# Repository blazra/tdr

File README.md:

# TDR
TDR using Lattice ECP5 High Data Rate Transceiver

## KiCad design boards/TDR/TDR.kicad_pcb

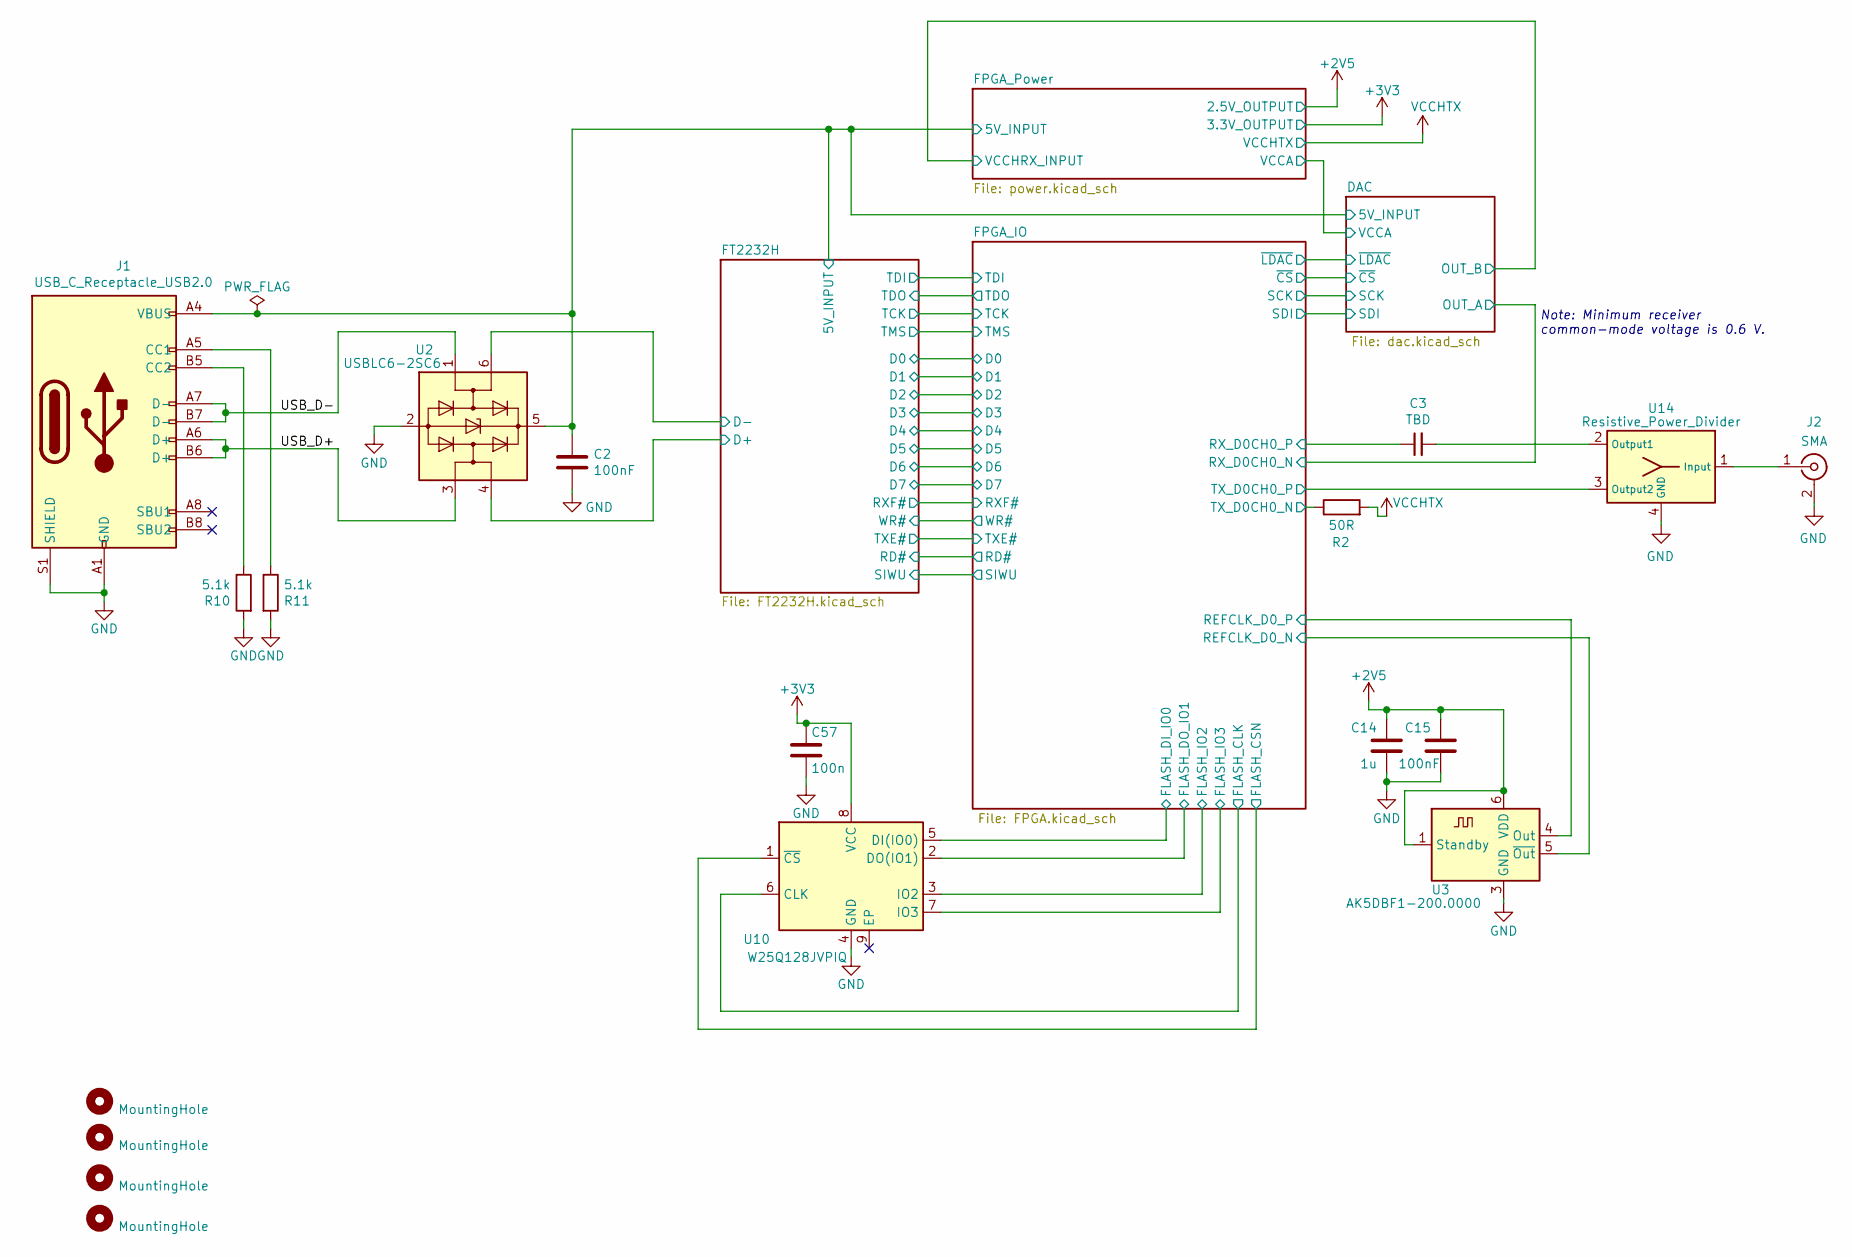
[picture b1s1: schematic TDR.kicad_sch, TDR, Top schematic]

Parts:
C2, C15: 100nF; C_0402_1005Metric
C3: TBD; C_0402_1005Metric
C14: 1u; C_0805_2012Metric
C57: 100n; C_0402_1005Metric
H1, H2, H3, H4: MountingHole; MountingHole_3.2mm_M3
J1: USB_C_Receptacle_USB2.0; USB_C_Receptacle_JAE_DX07S016
J2: SMA; Rosenberger_SMA_32K243-40ML5
R2: 50R; R_0402_1005Metric
R10, R11: 5.1k; R_0805_2012Metric
U2: USBLC6-2SC6; SOT-23-6
U3: AK5DBF1-200.0000; Oscillator_SMD_IDT_JS6-6_5.0x3.2mm_P1.27mm
U10: W25Q128JVPIQ; WSON-8-1EP_6x5mm_P1.27mm_EP3.4x4.3mm
U14: Resistive_Power_Divider; Susumu_PS2012G

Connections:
+2V5: C14.1, C15.1, U3.1 (Standby), U3.6 (VDD); also elsewhere on the board
+3V3: C57.1, U10.8 (VCC); also elsewhere on the board
/5V_INPUT: C2.1, J1.A4 (VBUS), J1.A9 (VBUS), J1.B4 (VBUS), J1.B9 (VBUS), U2.5 (VBUS); also elsewhere on the board
/D+: U2.4 (I/O2); also elsewhere on the board
/D-: U2.6 (I/O1); also elsewhere on the board
/FLASH_CLK: U10.6 (CLK); also elsewhere on the board
/FLASH_CSN: U10.1 (~CS); also elsewhere on the board
/FLASH_DI_IO0: U10.5 (DI(IO0)); also elsewhere on the board
/FLASH_DO_IO1: U10.2 (DO(IO1)); also elsewhere on the board
/FLASH_IO2: U10.3 (IO2); also elsewhere on the board
/FLASH_IO3: U10.7 (IO3); also elsewhere on the board
/REFCLK_D0_N: U3.5 (~Out); also elsewhere on the board
/REFCLK_D0_P: U3.4 (Out); also elsewhere on the board
/RX_D0CH0_P: C3.1; also elsewhere on the board
/TX_D0CH0_N: R2.1; also elsewhere on the board
/TX_D0CH0_P: U14.3 (Output2); also elsewhere on the board
/USB_D+: J1.A6 (D+), J1.B6 (D+), U2.3 (I/O2)
/USB_D-: J1.A7 (D-), J1.B7 (D-), U2.1 (I/O1)
GND: C2.2, C14.2, C15.2, C57.2, J1.A1 (GND), J1.A12 (GND), J1.B1 (GND), J1.B12 (GND), J1.S1 (SHIELD), J2.2 (Ext), R10.2, R11.2, U2.2 (GND), U3.3 (GND), U10.4 (GND), U14.4 (GND); also elsewhere on the board
unnamed: C3.2, U14.2 (Output1)
unnamed: J1.A5 (CC1), R11.1
unnamed: J1.B5 (CC2), R10.1
unnamed: J2.1 (In), U14.1 (Input)
VCCHTX: R2.2; also elsewhere on the board

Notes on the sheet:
Note: Minimum receiver common-mode voltage is 0.6 V.

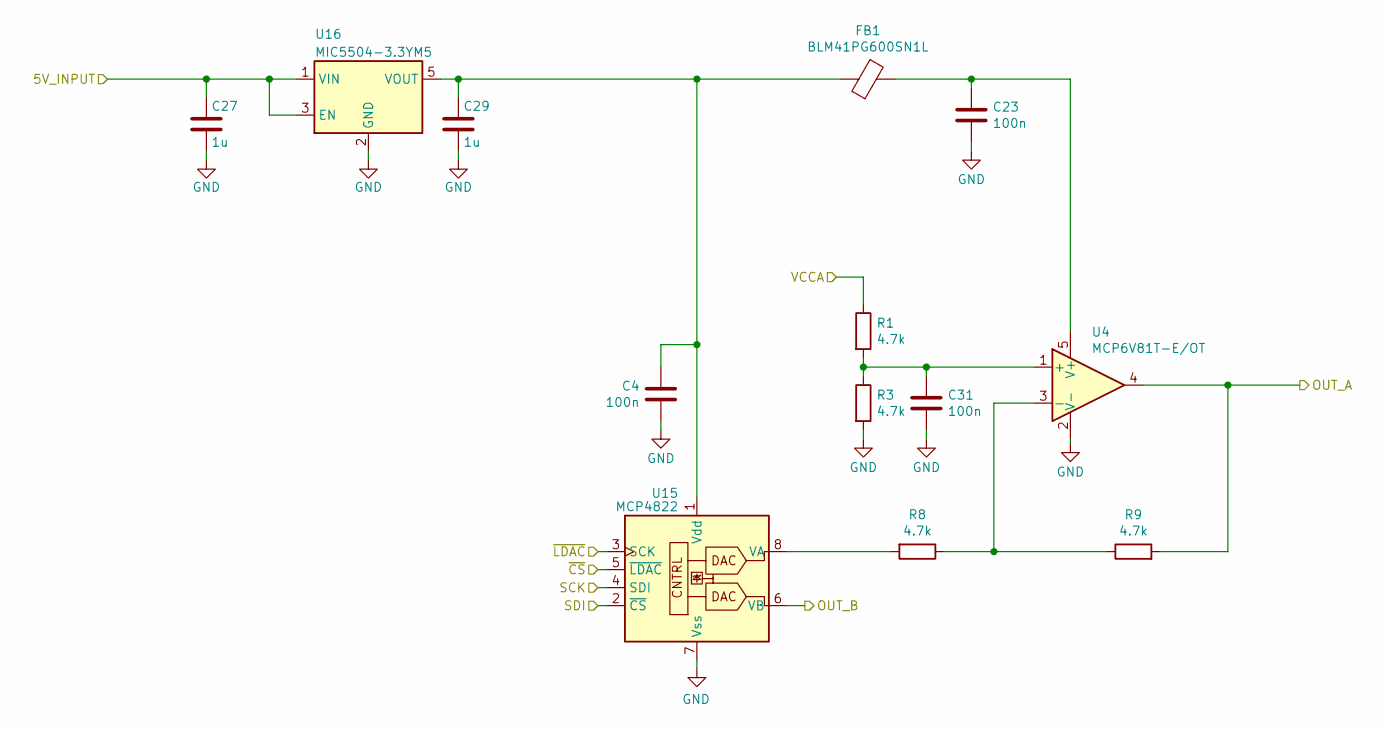
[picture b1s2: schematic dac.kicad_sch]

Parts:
C4, C23, C31: 100n; C_0402_1005Metric
C27, C29: 1u; C_0805_2012Metric
FB1: BLM41PG600SN1L; L_1806_4516Metric
R1, R3, R8, R9: 4.7k; R_0805_2012Metric
U4: MCP6V81T-E/OT; SOT-23-5
U15: MCP4822; MSOP-8_3x3mm_P0.65mm
U16: MIC5504-3.3YM5; SOT-23-5

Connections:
/5V_INPUT: C27.1, U16.1 (VIN), U16.3 (EN); also elsewhere on the board
/OUT_A: R9.2, U4.4; also elsewhere on the board
/OUT_B: U15.6 (VB); also elsewhere on the board
/SCK: U15.4 (SDI); also elsewhere on the board
/SDI: U15.2 (~CS); also elsewhere on the board
/VCCA: R1.1; also elsewhere on the board
/~CS: U15.5 (~LDAC); also elsewhere on the board
/~LDAC: U15.3 (SCK); also elsewhere on the board
GND: C4.2, C23.2, C27.2, C29.2, C31.1, R3.2, U4.2 (V-), U15.7 (Vss), U16.2 (GND); also elsewhere on the board
unnamed: C23.1, FB1.2, U4.5 (V+)
unnamed: C4.1, C29.1, FB1.1, U15.1 (Vdd), U16.5 (VOUT)
unnamed: C31.2, R1.2, R3.1, U4.1 (+)
unnamed: R8.1, R9.1, U4.3 (-)
unnamed: R8.2, U15.8 (VA)

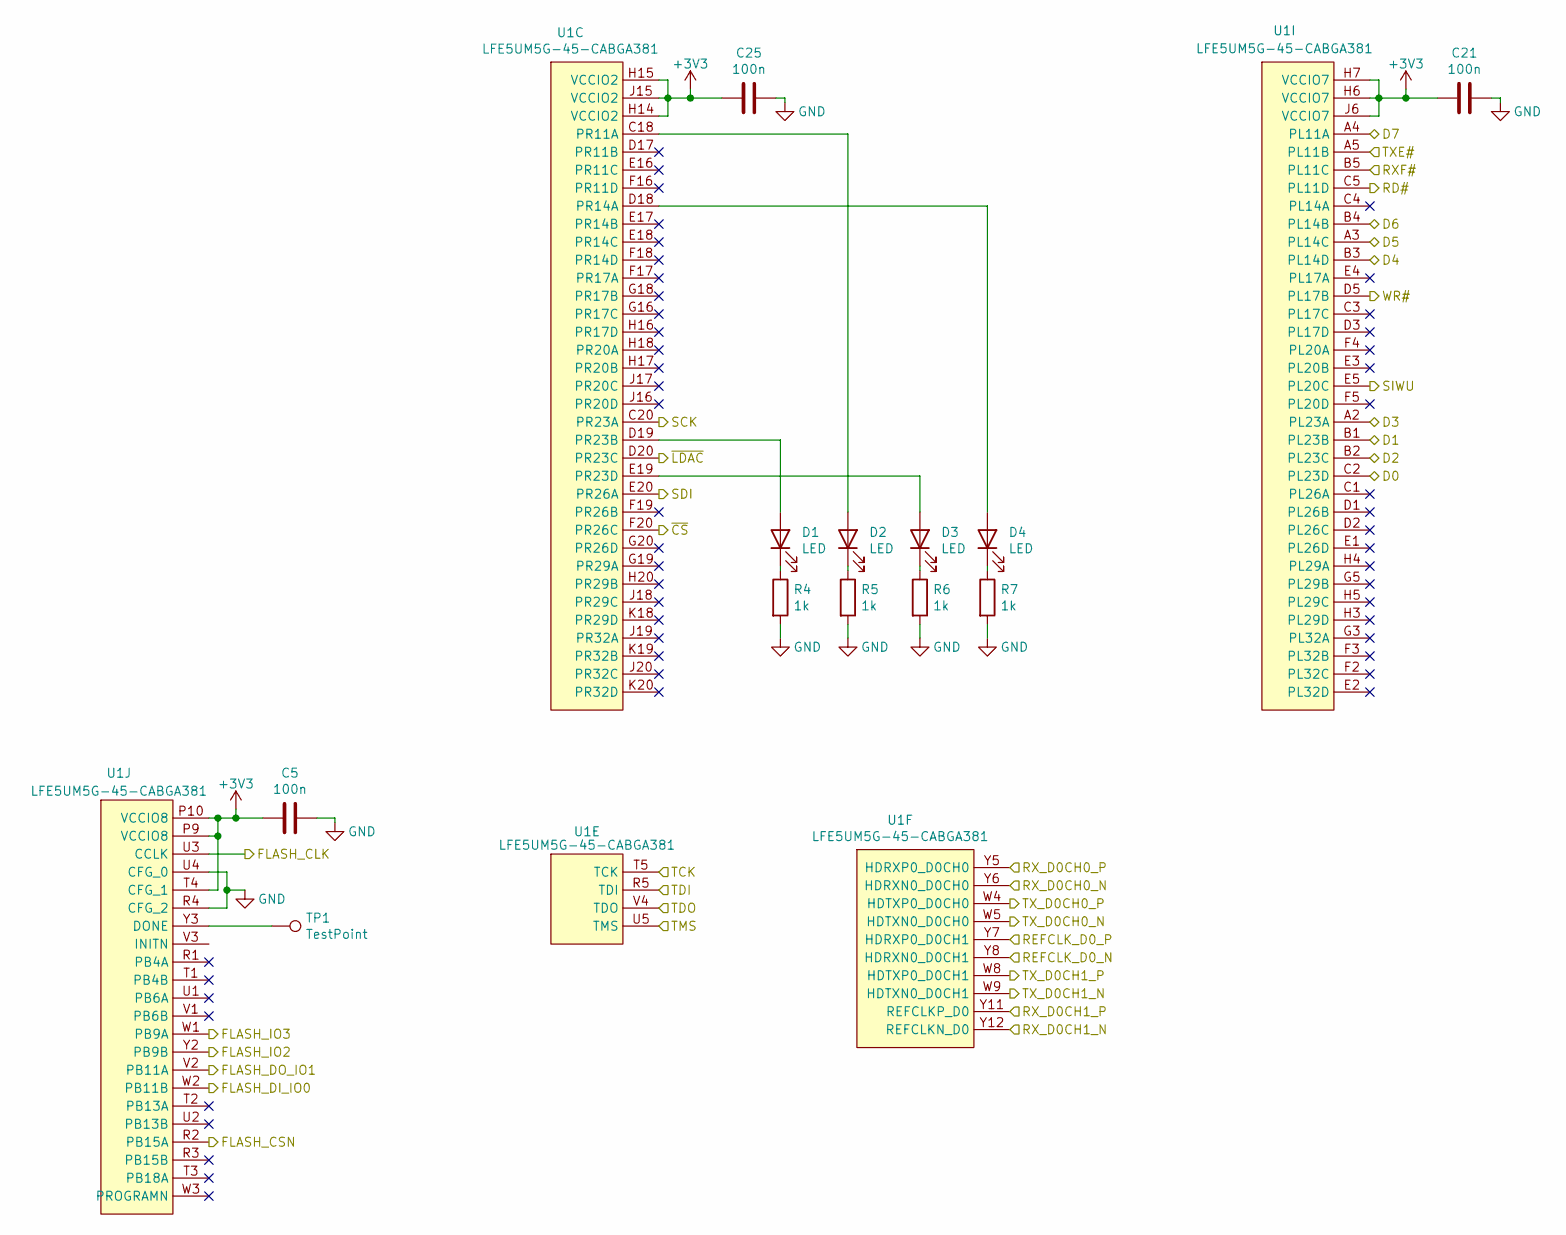
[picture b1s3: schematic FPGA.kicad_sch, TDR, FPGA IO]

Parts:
C5, C21, C25: 100n; C_0402_1005Metric
D1, D2, D3, D4: LED; LED_0805_2012Metric_Castellated
R4, R5, R6, R7: 1k; R_0805_2012Metric
TP1: TestPoint; TestPoint_Pad_D1.0mm
U1: LFE5UM5G-45-CABGA381; Lattice_caBGA-381_17.0x17.0mm_Layout20x20_P0.8mm_Ball0.4mm_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

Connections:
+3V3: C5.1, C21.1, C25.1, U1.H6 (VCCIO7), U1.H7 (VCCIO7), U1.H14 (VCCIO2), U1.H15 (VCCIO2), U1.J6 (VCCIO7), U1.J15 (VCCIO2), U1.P9 (VCCIO8), U1.P10 (VCCIO8), U1.T4 (CFG_1); also elsewhere on the board
/D0: U1.C2 (PL23D); also elsewhere on the board
/D1: U1.B1 (PL23B); also elsewhere on the board
/D2: U1.B2 (PL23C); also elsewhere on the board
/D3: U1.A2 (PL23A); also elsewhere on the board
/D4: U1.B3 (PL14D); also elsewhere on the board
/D5: U1.A3 (PL14C); also elsewhere on the board
/D6: U1.B4 (PL14B); also elsewhere on the board
/D7: U1.A4 (PL11A); also elsewhere on the board
/FLASH_CLK: U1.U3 (CCLK); also elsewhere on the board
/FLASH_CSN: U1.R2 (PB15A); also elsewhere on the board
/FLASH_DI_IO0: U1.W2 (PB11B); also elsewhere on the board
/FLASH_DO_IO1: U1.V2 (PB11A); also elsewhere on the board
/FLASH_IO2: U1.Y2 (PB9B); also elsewhere on the board
/FLASH_IO3: U1.W1 (PB9A); also elsewhere on the board
/FPGA_IO/RX_D0CH1_N: U1.Y12 (REFCLKN_D0)
/FPGA_IO/RX_D0CH1_P: U1.Y11 (REFCLKP_D0)
/FPGA_IO/TX_D0CH1_N: U1.W9 (HDTXN0_D0CH1)
/FPGA_IO/TX_D0CH1_P: U1.W8 (HDTXP0_D0CH1)
/OUT_A: U1.Y6 (HDRXN0_D0CH0); also elsewhere on the board
/RD#: U1.C5 (PL11D); also elsewhere on the board
/REFCLK_D0_N: U1.Y8 (HDRXN0_D0CH1); also elsewhere on the board
/REFCLK_D0_P: U1.Y7 (HDRXP0_D0CH1); also elsewhere on the board
/RXF#: U1.B5 (PL11C); also elsewhere on the board
/RX_D0CH0_P: U1.Y5 (HDRXP0_D0CH0); also elsewhere on the board
/SCK: U1.C20 (PR23A); also elsewhere on the board
/SDI: U1.E20 (PR26A); also elsewhere on the board
/SIWU: U1.E5 (PL20C); also elsewhere on the board
/TCK: U1.T5 (TCK); also elsewhere on the board
/TDI: U1.R5 (TDI); also elsewhere on the board
/TDO: U1.V4 (TDO); also elsewhere on the board
/TMS: U1.U5 (TMS); also elsewhere on the board
/TXE#: U1.A5 (PL11B); also elsewhere on the board
/TX_D0CH0_N: U1.W5 (HDTXN0_D0CH0); also elsewhere on the board
/TX_D0CH0_P: U1.W4 (HDTXP0_D0CH0); also elsewhere on the board
/WR#: U1.D5 (PL17B); also elsewhere on the board
/~CS: U1.F20 (PR26C); also elsewhere on the board
/~LDAC: U1.D20 (PR23C); also elsewhere on the board
GND: C5.2, C21.2, C25.2, R4.2, R5.2, R6.2, R7.2, U1.R4 (CFG_2), U1.U4 (CFG_0); also elsewhere on the board
unnamed: D1.1 (K), R4.1
unnamed: D1.2 (A), U1.D19 (PR23B)
unnamed: D2.1 (K), R5.1
unnamed: D2.2 (A), U1.C18 (PR11A)
unnamed: D3.1 (K), R6.1
unnamed: D3.2 (A), U1.E19 (PR23D)
unnamed: D4.1 (K), R7.1
unnamed: D4.2 (A), U1.D18 (PR14A)
unnamed: TP1.1, U1.Y3 (DONE)

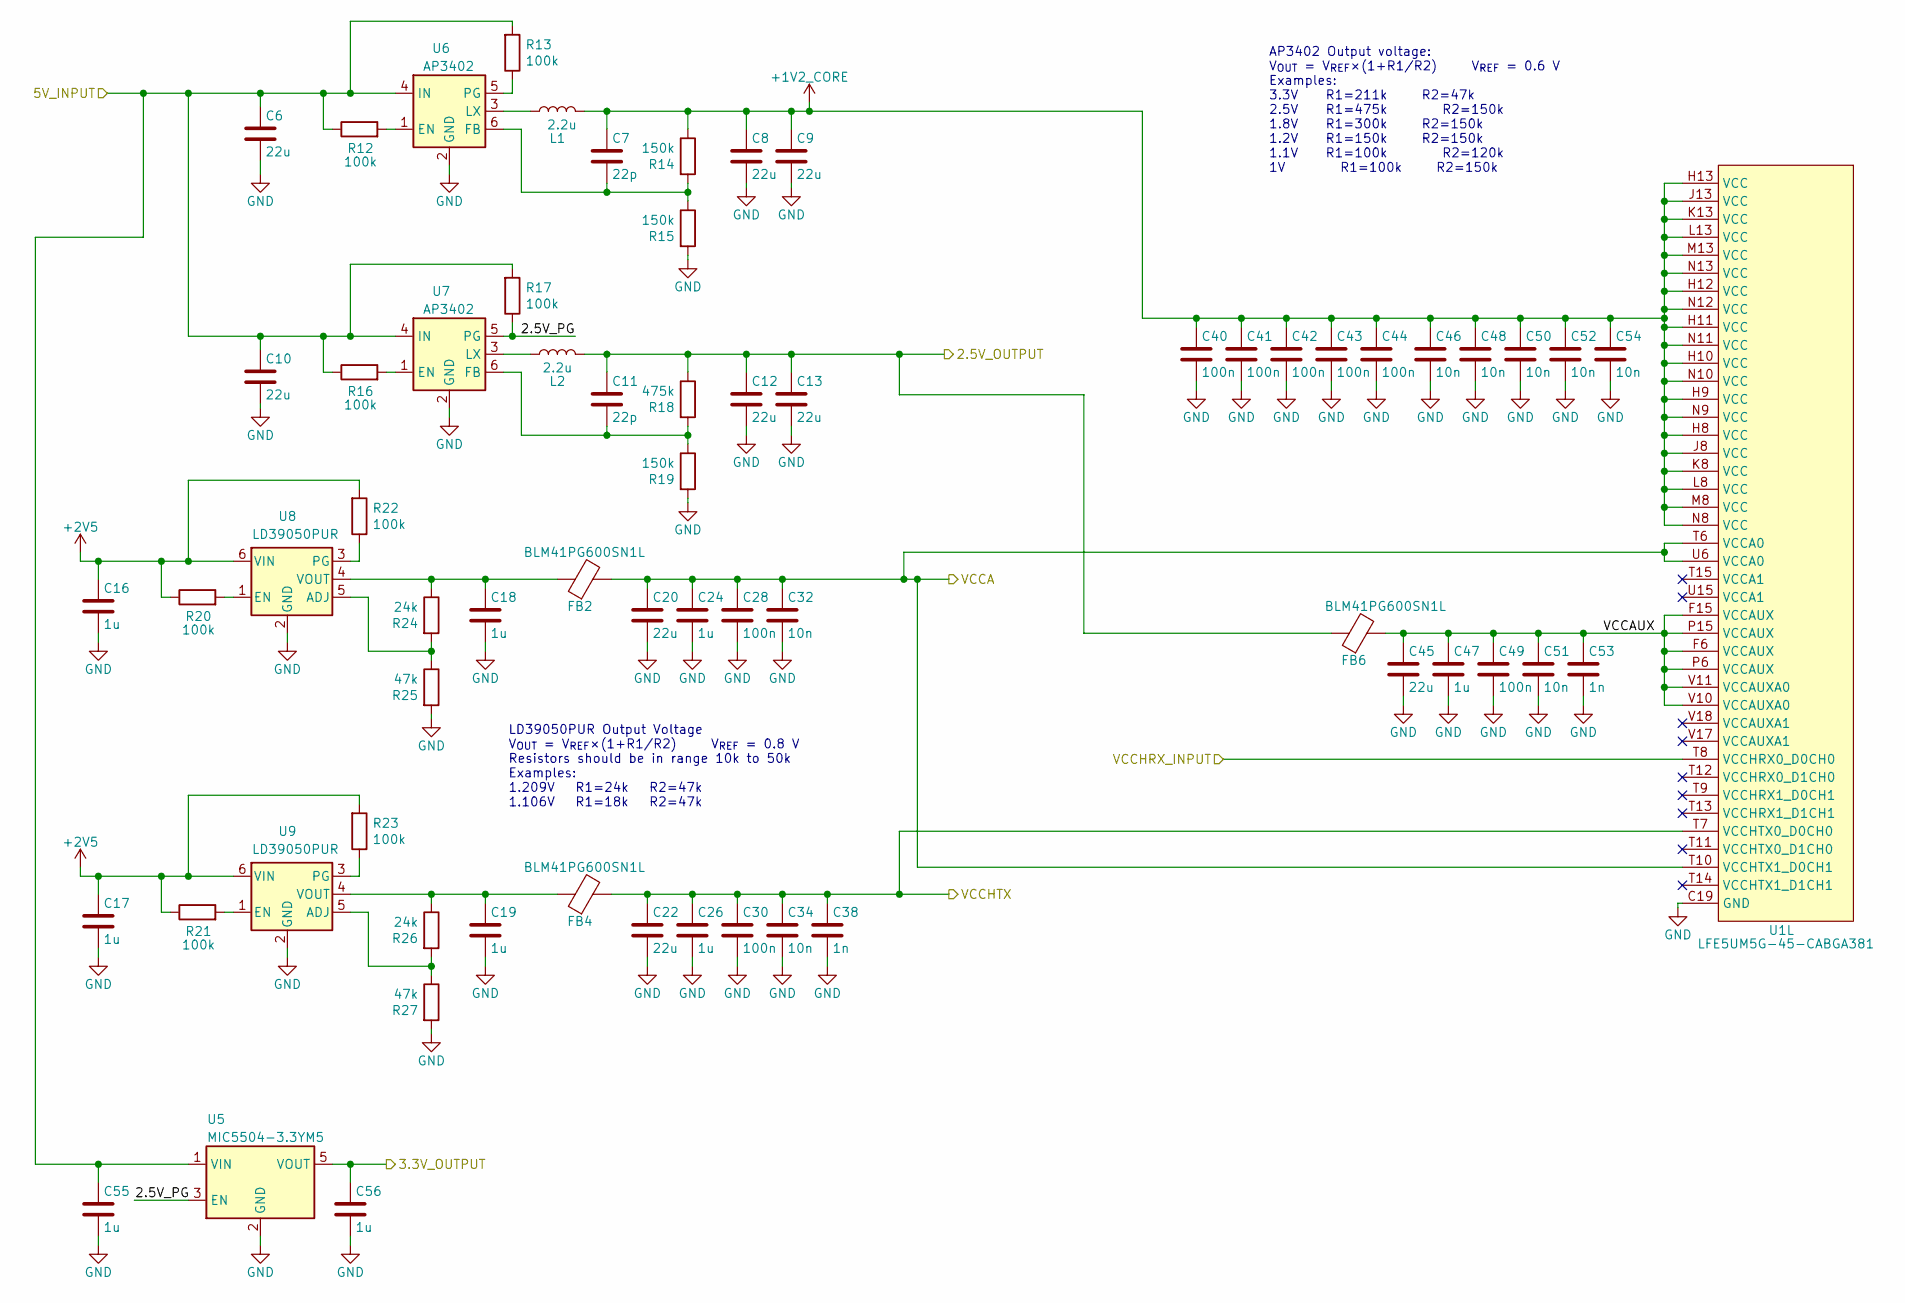
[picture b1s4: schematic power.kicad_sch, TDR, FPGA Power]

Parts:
C6, C8, C9, C10, C12, C13, C20, C22, C45: 22u; C_0805_2012Metric
C7, C11: 22p; C_0805_2012Metric
C16, C17, C18, C19, C24, C26, C47, C55, C56: 1u; C_0805_2012Metric
C28, C30, C40, C41, C42, C43, C44, C49: 100n; C_0402_1005Metric
C32, C34, C46, C48, C50, C51, C52, C54: 10n; C_0402_1005Metric
C38, C53: 1n; C_0402_1005Metric
FB2, FB4, FB6: BLM41PG600SN1L; L_1806_4516Metric
L1, L2: 2.2u; L_Ferrocore_HPI0530
R12, R13, R16, R17, R20, R21, R22, R23: 100k; R_0805_2012Metric
R14, R15, R19: 150k; R_0805_2012Metric
R18: 475k; R_0805_2012Metric
R24, R26: 24k; R_0805_2012Metric
R25, R27: 47k; R_0805_2012Metric
U1: LFE5UM5G-45-CABGA381; Lattice_caBGA-381_17.0x17.0mm_Layout20x20_P0.8mm_Ball0.4mm_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
U5: MIC5504-3.3YM5; SOT-23-5
U6, U7: AP3402; SOT-23-6
U8, U9: LD39050PUR; DFN-6-1EP_3x3mm_P0.95mm_EP1.7x2.6mm

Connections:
+1V2_CORE: C7.1, C8.1, C9.1, C40.1, C41.1, C42.1, C43.1, C44.1, C46.1, C48.1, C50.1, C52.1, C54.1, L1.2, R14.1, U1.H8 (VCC), U1.H9 (VCC), U1.H10 (VCC), U1.H11 (VCC), U1.H12 (VCC), U1.H13 (VCC), U1.J8 (VCC), U1.J13 (VCC), U1.K8 (VCC), U1.K13 (VCC), U1.L8 (VCC), U1.L13 (VCC), U1.M8 (VCC), U1.M13 (VCC), U1.N8 (VCC), U1.N9 (VCC), U1.N10 (VCC), U1.N11 (VCC), U1.N12 (VCC), U1.N13 (VCC)
+2V5: C11.1, C12.1, C13.1, C16.1, C17.1, FB6.1, L2.2, R18.1, R20.1, R21.1, R22.2, R23.2, U8.6 (VIN), U9.6 (VIN); also elsewhere on the board
+3V3: C56.1, U5.5 (VOUT); also elsewhere on the board
/5V_INPUT: C6.1, C10.1, C55.1, R12.1, R13.2, R16.1, R17.2, U5.1 (VIN), U6.4 (IN), U7.4 (IN); also elsewhere on the board
/FPGA_Power/2.5V_PG: R17.1, U5.3 (EN), U7.5 (PG)
/FPGA_Power/VCCAUX: C45.1, C47.1, C49.1, C51.1, C53.1, FB6.2, U1.F6 (VCCAUX), U1.F15 (VCCAUX), U1.P6 (VCCAUX), U1.P15 (VCCAUX), U1.V10 (VCCAUXA0), U1.V11 (VCCAUXA0)
/OUT_B: U1.T8 (VCCHRX0_D0CH0); also elsewhere on the board
/VCCA: C20.1, C24.1, C28.1, C32.1, FB2.2, U1.T6 (VCCA0), U1.T10 (VCCHTX1_D0CH1), U1.U6 (VCCA0); also elsewhere on the board
GND: C6.2, C8.2, C9.2, C10.2, C12.2, C13.2, C16.2, C17.2, C18.2, C19.2, C20.2, C22.2, C24.2, C26.2, C28.2, C30.2, C32.2, C34.2, C38.2, C40.2, C41.2, C42.2, C43.2, C44.2, C45.2, C46.2, C47.2, C48.2, C49.2, C50.2, C51.2, C52.2, C53.2, C54.2, C55.2, C56.2, R15.2, R19.2, R25.2, R27.2, U1.B7 (GND), U1.B14 (GND), U1.C19 (GND), U1.D4 (GND), U1.F7 (GND), U1.F8 (GND), U1.F13 (GND), U1.F14 (GND), U1.G4 (GND), U1.G6 (GND), U1.G7 (GND), U1.G8 (GND), U1.G9 (GND), U1.G10 (GND), U1.G11 (GND), U1.G12 (GND), U1.G13 (GND), U1.G14 (GND), U1.G15 (GND), U1.G17 (GND), U1.H19 (GND), U1.J2 (GND), U1.J7 (GND), U1.J9 (GND), U1.J10 (GND), U1.J11 (GND), U1.J12 (GND), U1.J14 (GND), U1.K6 (GND), U1.K7 (GND), U1.K9 (GND), U1.K10 (GND), U1.K11 (GND), U1.K12 (GND), U1.K14 (GND), U1.K15 (GND), U1.L9 (GND), U1.L10 (GND), U1.L11 (GND), U1.L12 (GND), U1.M2 (GND), U1.M7 (GND), U1.M9 (GND), U1.M10 (GND), U1.M11 (GND), U1.M12 (GND), U1.M14 (GND), U1.M16 (GND), U1.N6 (GND), U1.N7 (GND), U1.N14 (GND), U1.N15 (GND), U1.P7 (GND), U1.P8 (GND), U1.P11 (GND), U1.P12 (GND), U1.P13 (GND), U1.P14 (GND), U1.R19 (GND), U1.U7 (GND), U1.U8 (GND), U1.U9 (GND), U1.U10 (GND), U1.U11 (GND), U1.U12 (GND), U1.U13 (GND), U1.U14 (GND), U1.V5 (GND), U1.V6 (GND), U1.V7 (GND), U1.V8 (GND), U1.V9 (GND), U1.V12 (GND), U1.V13 (GND), U1.V14 (GND), U1.V15 (GND), U1.V16 (GND), U1.V19 (GND), U1.V20 (GND), U1.W6 (GND), U1.W7 (GND), U1.W12 (GND), U1.W15 (GND), U1.W16 (GND), U1.W19 (GND), U5.2 (GND), U6.2 (GND), U7.2 (GND), U8.2 (GND), U9.2 (GND); also elsewhere on the board
unnamed: C7.2, R14.2, R15.1, U6.6 (FB)
unnamed: C11.2, R18.2, R19.1, U7.6 (FB)
unnamed: C18.1, FB2.1, R24.1, U8.4 (VOUT)
unnamed: C19.1, FB4.1, R26.1, U9.4 (VOUT)
unnamed: L1.1, U6.3 (LX)
unnamed: L2.1, U7.3 (LX)
unnamed: R12.2, U6.1 (EN)
unnamed: R13.1, U6.5 (PG)
unnamed: R16.2, U7.1 (EN)
unnamed: R20.2, U8.1 (EN)
unnamed: R21.2, U9.1 (EN)
unnamed: R22.1, U8.3 (PG)
unnamed: R23.1, U9.3 (PG)
unnamed: R24.2, R25.1, U8.5 (ADJ)
unnamed: R26.2, R27.1, U9.5 (ADJ)
VCCHTX: C22.1, C26.1, C30.1, C34.1, C38.1, FB4.2, U1.T7 (VCCHTX0_D0CH0); also elsewhere on the board

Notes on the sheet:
LD39050PUR Output Voltage V_{OUT} = V_{REF}×(1+R1/R2) V_{REF} = 0.8 V Resistors should be in range 10k to 50k Examples: 1.209V R1=24k R2=47k 1.106V R1=18k R2=47k
AP3402 Output voltage: V_{OUT} = V_{REF}×(1+R1/R2) V_{REF} = 0.6 V Examples: 3.3V R1=211k R2=47k 2.5V R1=475k R2=150k 1.8V R1=300k R2=150k 1.2V R1=150k R2=150k 1.1V R1=100k R2=120k 1V R1=100k R2=150k

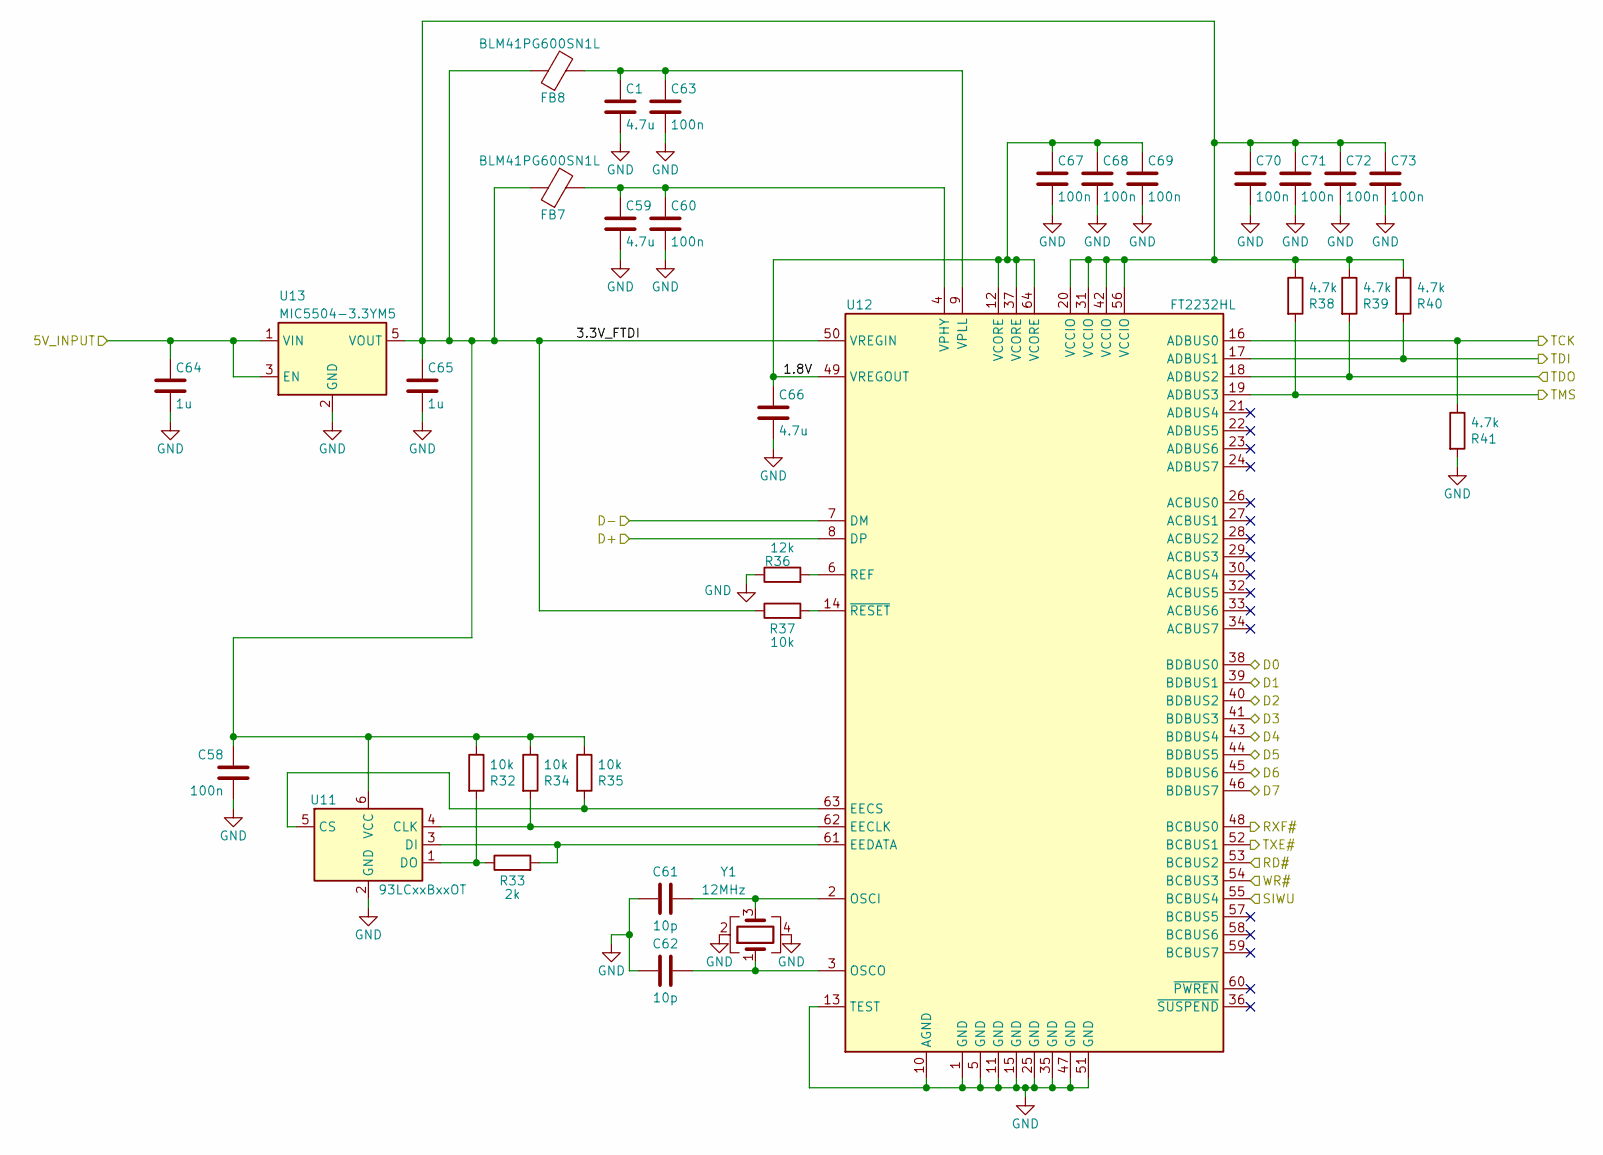
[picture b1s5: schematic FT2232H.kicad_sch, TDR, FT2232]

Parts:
C1, C59, C66: 4.7u; C_0805_2012Metric
C58, C60, C63, C67, C68, C69, C70, C71, C72, C73: 100n; C_0402_1005Metric
C61, C62: 10p; C_0805_2012Metric
C64, C65: 1u; C_0805_2012Metric
FB7, FB8: BLM41PG600SN1L; L_1806_4516Metric
R32, R34, R35, R37: 10k; R_0805_2012Metric
R33: 2k; R_0805_2012Metric
R36: 12k; R_0805_2012Metric
R38, R39, R40, R41: 4.7k; R_0805_2012Metric
U11: 93LCxxBxxOT; SOT-23-6
U12: FT2232HL; LQFP-64_10x10mm_P0.5mm
U13: MIC5504-3.3YM5; SOT-23-5
Y1: 12MHz; Crystal_SMD_3225-4Pin_3.2x2.5mm

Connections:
/5V_INPUT: C64.1, U13.1 (VIN), U13.3 (EN); also elsewhere on the board
/D0: U12.38 (BDBUS0); also elsewhere on the board
/D1: U12.39 (BDBUS1); also elsewhere on the board
/D2: U12.40 (BDBUS2); also elsewhere on the board
/D3: U12.41 (BDBUS3); also elsewhere on the board
/D4: U12.43 (BDBUS4); also elsewhere on the board
/D5: U12.44 (BDBUS5); also elsewhere on the board
/D6: U12.45 (BDBUS6); also elsewhere on the board
/D7: U12.46 (BDBUS7); also elsewhere on the board
/D+: U12.8 (DP); also elsewhere on the board
/D-: U12.7 (DM); also elsewhere on the board
/FT2232H/1.8V: C66.1, C67.1, C68.1, C69.1, U12.12 (VCORE), U12.37 (VCORE), U12.49 (VREGOUT), U12.64 (VCORE)
/FT2232H/3.3V_FTDI: C58.2, C65.1, C70.1, C71.1, C72.1, C73.1, FB7.1, FB8.1, R32.1, R34.1, R35.1, R37.1, R38.1, R39.1, R40.1, U11.6 (VCC), U12.20 (VCCIO), U12.31 (VCCIO), U12.42 (VCCIO), U12.50 (VREGIN), U12.56 (VCCIO), U13.5 (VOUT)
/RD#: U12.53 (BCBUS2); also elsewhere on the board
/RXF#: U12.48 (BCBUS0); also elsewhere on the board
/SIWU: U12.55 (BCBUS4); also elsewhere on the board
/TCK: R41.1, U12.16 (ADBUS0); also elsewhere on the board
/TDI: R40.2, U12.17 (ADBUS1); also elsewhere on the board
/TDO: R39.2, U12.18 (ADBUS2); also elsewhere on the board
/TMS: R38.2, U12.19 (ADBUS3); also elsewhere on the board
/TXE#: U12.52 (BCBUS1); also elsewhere on the board
/WR#: U12.54 (BCBUS3); also elsewhere on the board
GND: C1.2, C58.1, C59.2, C60.2, C61.1, C62.1, C63.2, C64.2, C65.2, C66.2, C67.2, C68.2, C69.2, C70.2, C71.2, C72.2, C73.2, R36.1, R41.2, U11.2 (GND), U12.1 (GND), U12.5 (GND), U12.10 (AGND), U12.11 (GND), U12.13 (TEST), U12.15 (GND), U12.25 (GND), U12.35 (GND), U12.47 (GND), U12.51 (GND), U13.2 (GND), Y1.2, Y1.4; also elsewhere on the board
unnamed: C1.1, C63.1, FB8.2, U12.9 (VPLL)
unnamed: C59.1, C60.1, FB7.2, U12.4 (VPHY)
unnamed: C61.2, U12.2 (OSCI), Y1.3
unnamed: C62.2, U12.3 (OSCO), Y1.1
unnamed: R32.2, R33.1, U11.1 (DO)
unnamed: R33.2, U11.3 (DI), U12.61 (EEDATA)
unnamed: R34.2, U11.4 (CLK), U12.62 (EECLK)
unnamed: R35.2, U11.5 (CS), U12.63 (EECS)
unnamed: R36.2, U12.6 (REF)
unnamed: R37.2, U12.14 (~RESET)

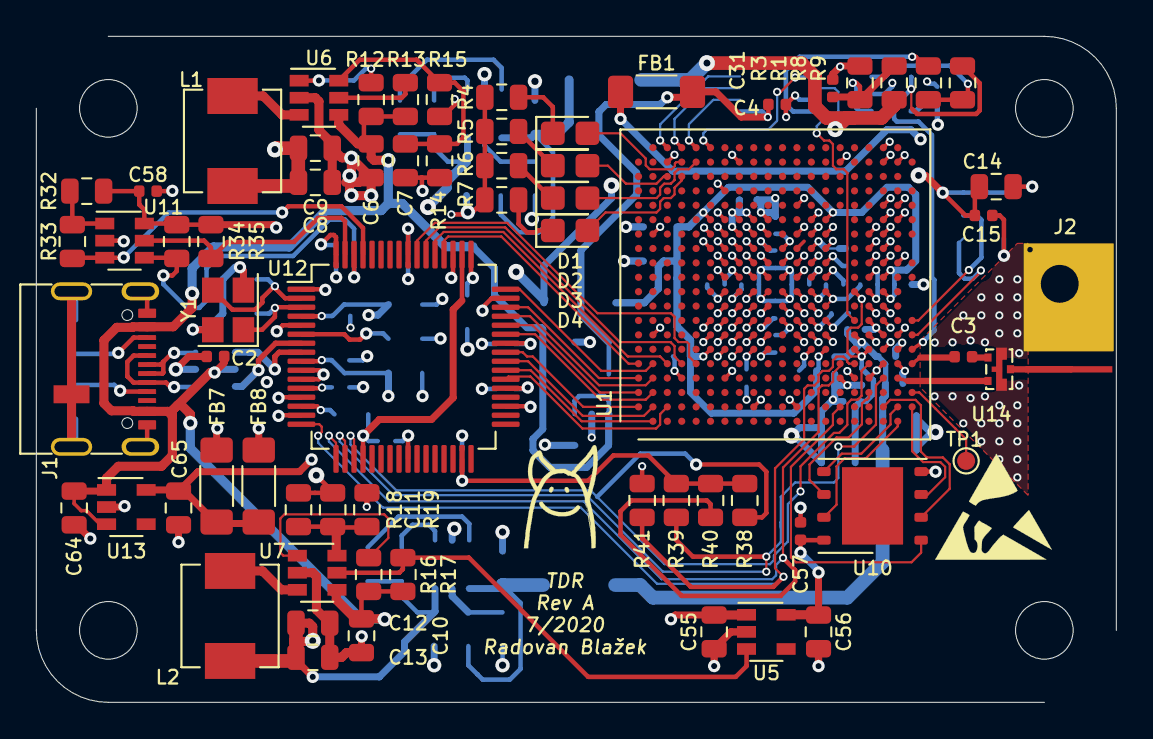
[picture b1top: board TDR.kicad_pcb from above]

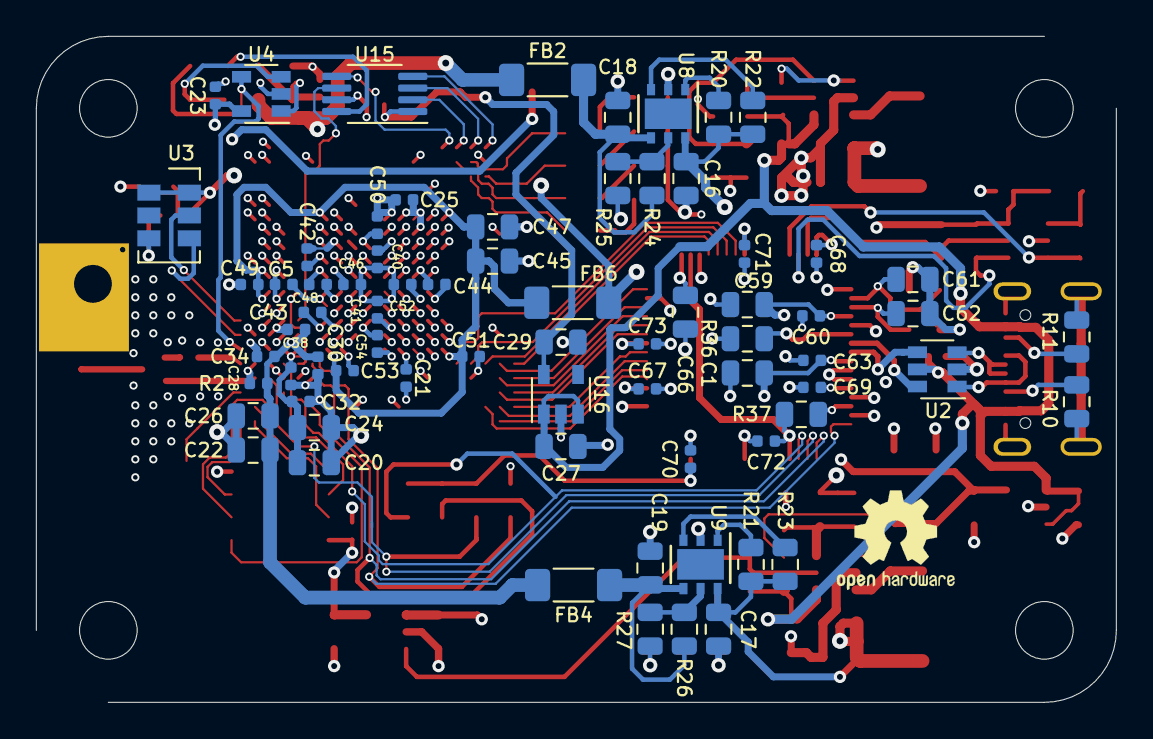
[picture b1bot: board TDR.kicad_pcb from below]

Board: 4 copper layers, 60.0 x 37.0 mm, 141 parts (71 on the bottom side), 92 nets.

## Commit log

2020-04-02 Set theme jekyll-theme-minimal
2020-04-03 docs: highlight: rouge
2020-04-04 add: github highlight css
2020-04-04 docs: edit code block font
2020-04-04 docs: add ibom
2020-06-30 Add versa-ecp5 proof of concept gateware and sw
    This works using SERDES running at 2.5 Gbps for RX and Low Data Rate
    port for TX.
2020-06-30 Add kicad pcb files
2020-07-06 change crystal footprint and roughly finish schematic
2020-07-06 change usb footprint, route a few connections
2020-07-07 connect fpga vccio to 3.3V, add decoupling, route some tracks
2020-07-09 route almost all nets except VCCA, VCCAUX and maybe some others
2020-07-10 solved DRC errors and routed few more nets
2020-07-10 add LEDs, only 9 unconnected items remaining
2020-07-10 change BGA dogbone stringer width to 0.2 mm, 7 unconncted
2020-07-10 finish routing
2020-07-10 finishing touches on the silkscreen
2020-07-10 hopefully PCB is done
2020-07-14 add gerbers, this is revision 1
2020-07-14 update ibom
2020-08-01 Add LD39050PUR feedback resistor values, fixed regulator enable
    Fixes #1
